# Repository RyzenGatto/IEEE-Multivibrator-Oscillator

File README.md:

# IEEE-Astable Multivibrator 
Soldering Workshop for IEEE's University of Arizona Student Chapter

## Renders and Diagrams 

These are the 3D renders of the PCB. Raw STEP and Gerber files are available in the repository.

**Top**

**Bottom**

**PCB layout from KiCad**

This is a diagram of the circuit.

# Parts
Resistors are 10k where used. Capacitors are 20uF 
Both LED's should be the same color/same voltage for equal oscillation.
Input voltage is designed to be 3 volts from a coin cell battery. More voltage would require resistors to the LEDs.

The transistors used are BC547 and act as switches in this circuit. They are NPN transistors which is wanted because we want the transistors to open when voltage is applied to it, or when voltage is high.

# How it works

The capacitors are connected to the bases of the opposite transistor. As the capacitor voltage rises to 700mV, the attached transistor will close and the capacitor will discharge. This is due to the capacitor on the same side as the open transistor experiencing a drop in current, which can be visualized in a simulation of the circuit.  At the same time, the capacitor controlling the opposite transistor gains voltage and opens. Very cool.

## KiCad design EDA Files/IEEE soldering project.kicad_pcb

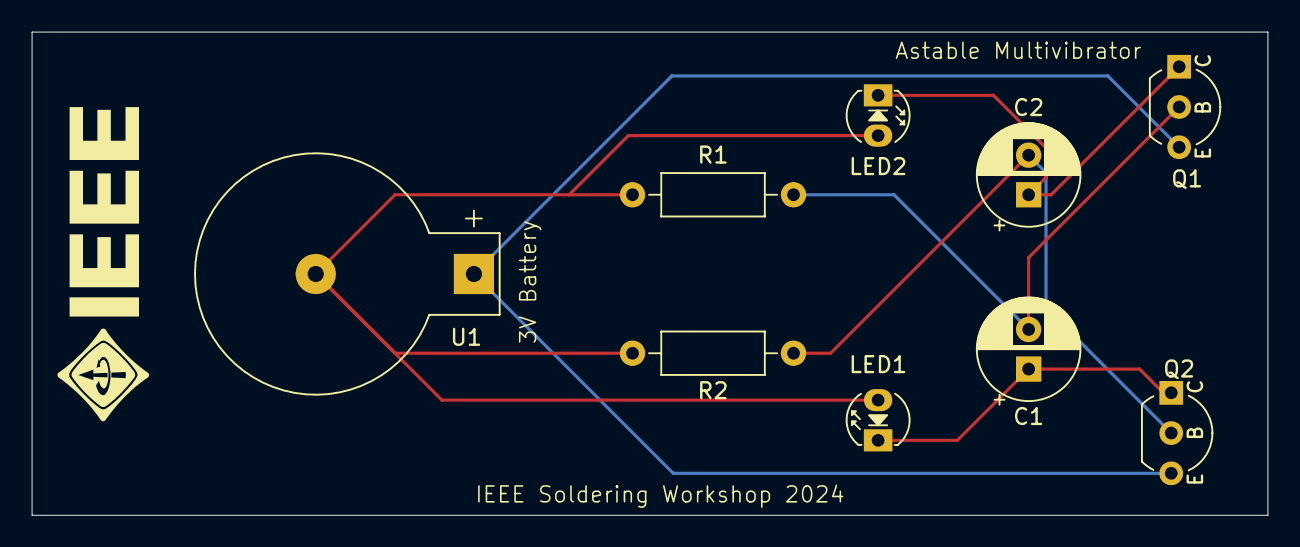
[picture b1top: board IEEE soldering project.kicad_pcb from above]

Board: 2 copper layers, 78.0 x 30.5 mm, 9 parts (0 on the bottom side), 6 nets.

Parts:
C1, C2: 220uF_10V; CP_Radial_D6.3mm_P2.50mm
LED1, LED2: LED_3mm; LED_D3.0mm
Q1, Q2: BC547; TO-92_Inline_Wide_CBE
R1, R2: 10k; R_Axial_DIN0207_L6.3mm_D2.5mm_P10.16mm_Horizontal
U1: BatteryHolder_Keystone_500

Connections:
unnamed: LED1.2 (A), LED2.2 (A), R1.2, R2.2, U1.2 (-)
unnamed: C1.1, LED1.1 (K), Q2.1 (C)
unnamed: C2.1, LED2.1 (K), Q1.1 (C)
unnamed: C1.2, Q1.2 (B), R1.1
unnamed: Q1.3 (E), Q2.3 (E), U1.1 (+)
unnamed: C2.2, Q2.2 (B), R2.1

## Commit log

2024-10-02 Add files via upload
    Writeup assets
2024-10-02 Update README.md
    This isn't done, I'm very tired.
2024-10-12 Add files via upload
    Updated and cleaned up the PCB. USE THIS FILE.
2024-10-12 Add files via upload
    V2 Gerbers!
2024-10-12 Add files via upload
    V2!!!
2024-10-12 Create LICENSE
